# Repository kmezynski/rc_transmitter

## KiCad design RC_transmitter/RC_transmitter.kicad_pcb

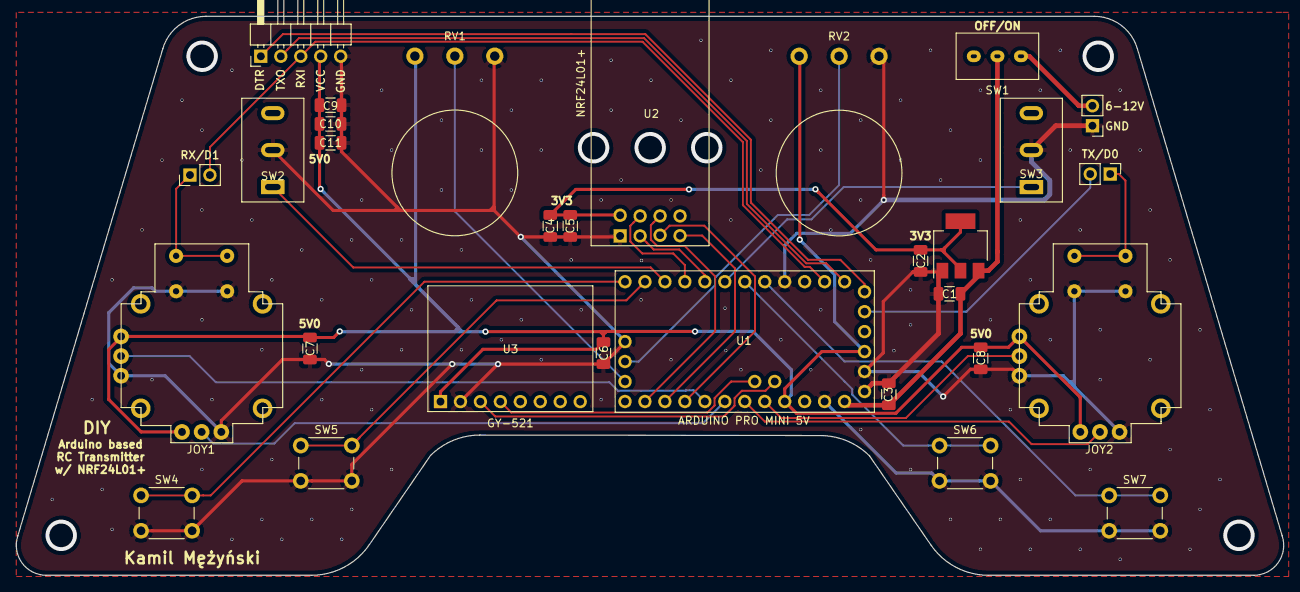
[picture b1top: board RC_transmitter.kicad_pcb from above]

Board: 2 copper layers, 161.3 x 71.1 mm, 30 parts (0 on the bottom side), 29 nets.

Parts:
C1, C2: 10uF; C_1206_3216Metric
C3, C6, C7, C8, C10, C11: 100nF; C_1206_3216Metric
C4: 1nF; C_1206_3216Metric
C5: 10nF; C_1206_3216Metric
C9: 4.7uF; C_1206_3216Metric
J1: Conn_01x05; PinHeader_1x05_P2.54mm_Horizontal
J2, J3, J4: Conn_01x02; PinHeader_1x02_P2.54mm_Vertical
JOY1, JOY2: Joystick
RV1, RV2: R_POT; Potentiometer_THT_vertical
SW1: SW_SPDT; SPDT_SS02-12F20
SW2, SW3: SW_SPDT; SPDT_MTS-102
SW4, SW5, SW6, SW7: SW_Push; SW_PUSH_6mm_H13mm
U1: Arduino_Pro_Mini
U2: NRF24L01_Breakout; NRF24L01+
U3: GY-521_MOD; GY-521_module
VR1: Volt_Reg_3.3; SOT-223-3_TabPin2

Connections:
3.3V: C2.1, C4.1, C5.1, U2.2, VR1.2
+BATT: C1.1, C3.1, SW1.1, U1.18, VR1.3
A6: RV2.2, U1.19
A7: RV1.2, U1.22
CE: U1.9, U2.3
CSN: U1.10, U2.4
D2: SW7.1, U1.32
D3: SW6.1, U1.1
D4: SW3.1, U1.2
D7: SW2.1, U1.11
D8: SW5.1, U1.12
D9: SW4.1, U1.13
DTR: J1.1, U1.20
GND: C1.2, C2.2, C3.2, C4.2, C5.2, C6.2, C7.2, C8.2, C9.2, C10.2, C11.2, J1.5, J2.1, JOY1.3, JOY1.4, JOY1.5, JOY2.3, JOY2.4, JOY2.5, RV1.3, RV2.3, SW2.2, SW3.2, SW4.2, SW5.2, SW6.2, SW7.2, U1.3, U1.5, U1.21, U2.1, U3.2, VR1.1
MISO: U1.16, U2.7
MOSI: U1.15, U2.6
unnamed: J2.2, SW1.2
RXI: J1.3, J3.2, U1.30
SCK: U1.17, U2.5
SCL: U1.28, U3.3
SDA: U1.27, U3.4
TXO: J1.2, J4.2, U1.31
VCC: C6.1, C7.1, C8.1, C9.1, C10.1, C11.1, J1.4, JOY1.1, JOY1.2, JOY2.1, JOY2.2, RV1.1, RV2.1, U1.4, U1.6, U3.1
VRx_1: JOY1.6, U1.23
VRx_2: JOY2.6, U1.26
VRy_1: JOY1.7, U1.24
VRy_2: JOY2.7, U1.25
jRXI: J3.1, JOY1.8
jTXO: J4.1, JOY2.8

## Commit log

2020-05-17 pcb layout
2020-05-17 pcb schematic
2020-05-17 ATmega328P datasheet
2020-05-17 switches datasheets
2020-05-17 remaining datasheets
2020-05-17 RC transmitter library
2020-05-17 RC transmitter gerber files
2020-05-17 RC transmitter 3d models
2020-05-17 RC transmitter final version
2020-05-21 update LICENSE
